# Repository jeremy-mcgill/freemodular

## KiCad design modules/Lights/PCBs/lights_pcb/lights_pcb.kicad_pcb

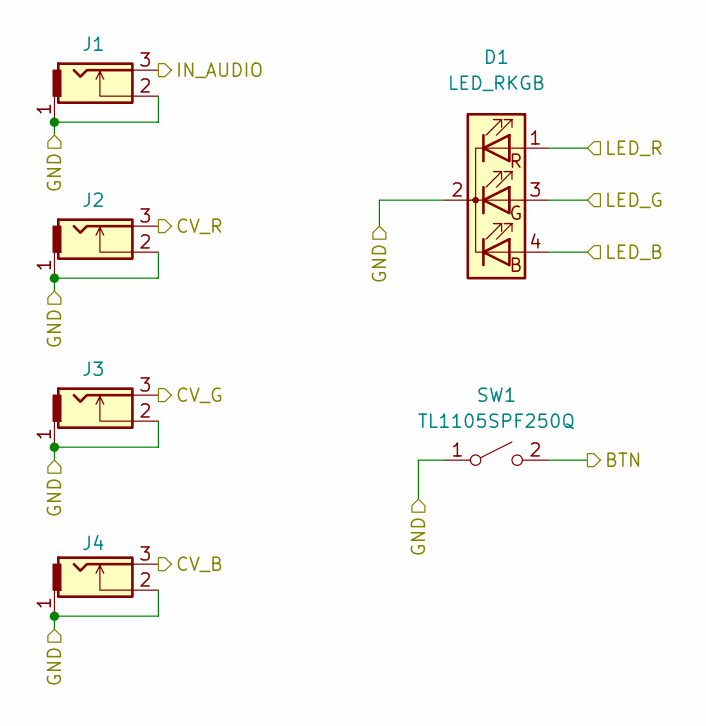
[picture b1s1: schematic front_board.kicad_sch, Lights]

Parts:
D1: LED_RKGB; LED_D5.0mm-4_RGB
J1, J2, J3, J4: THONKICONN
SW1: TL1105SPF250Q; SW_PUSH_6mm_H13mm

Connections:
/Front Board/BTN: SW1.2 (B); also elsewhere on the board
/Front Board/CV_B: J4.3; also elsewhere on the board
/Front Board/CV_G: J3.3; also elsewhere on the board
/Front Board/CV_R: J2.3; also elsewhere on the board
/Front Board/GND: D1.2 (K), J1.1, J1.2, J2.1, J2.2, J3.1, J3.2, J4.1, J4.2, SW1.1 (A); also elsewhere on the board
/Front Board/IN_AUDIO: J1.3; also elsewhere on the board
/Front Board/LED_B: D1.4 (BA); also elsewhere on the board
/Front Board/LED_G: D1.3 (GA); also elsewhere on the board
/Front Board/LED_R: D1.1 (RA); also elsewhere on the board

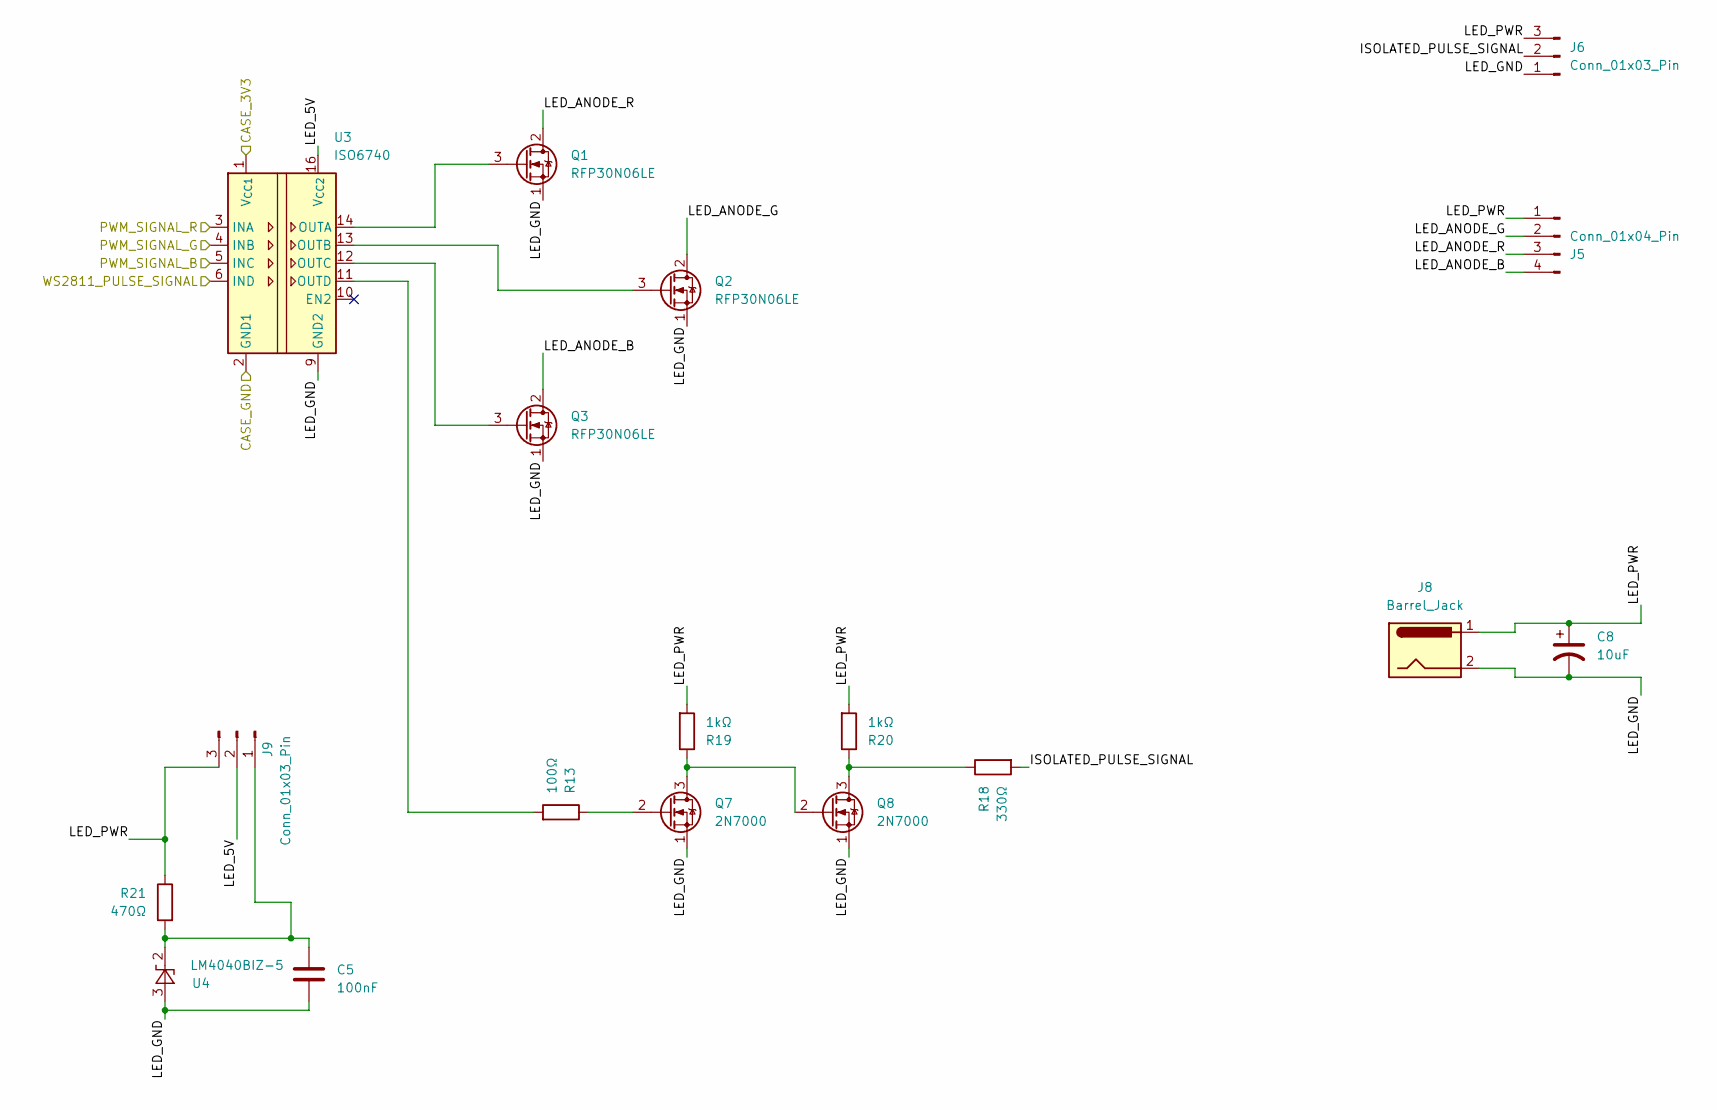
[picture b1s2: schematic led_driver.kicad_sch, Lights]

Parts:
C5: 100nF; C_Disc_D5.0mm_W2.5mm_P5.00mm
C8: 10uF; CP_Radial_D4.0mm_P1.50mm
J5: Conn_01x04_Pin; PinSocket_1x04_P2.54mm_Vertical
J6, J9: Conn_01x03_Pin; PinSocket_1x03_P2.54mm_Vertical
J8: Barrel_Jack; BarrelJack_Wuerth_6941xx301002
Q1, Q2, Q3: RFP30N06LE; TO-220-3_Vertical
Q7, Q8: 2N7000; TO-92_Inline
R13: 100Ω; R_Axial_DIN0207_L6.3mm_D2.5mm_P7.62mm_Horizontal
R18: 330Ω; R_Axial_DIN0207_L6.3mm_D2.5mm_P7.62mm_Horizontal
R19, R20: 1kΩ; R_Axial_DIN0207_L6.3mm_D2.5mm_P7.62mm_Horizontal
R21: 470Ω; R_Axial_DIN0207_L6.3mm_D2.5mm_P7.62mm_Horizontal
U3: ISO6740; SOIC-16W_7.5x10.3mm_P1.27mm
U4: LM4040BIZ-5; TO-92_Inline_Wide

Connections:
/Rear Board/+3.3V: U3.1 (V_{CC1}); also elsewhere on the board
/Rear Board/GND: U3.2 (GND1), U3.8 (GND1); also elsewhere on the board
/Rear Board/LED Driver/ISOLATED_PULSE_SIGNAL: J6.2, R18.2
/Rear Board/LED Driver/LED_5V: J9.2, U3.16 (V_{CC2})
/Rear Board/LED Driver/LED_ANODE_B: J5.4, Q3.2 (D)
/Rear Board/LED Driver/LED_ANODE_G: J5.2, Q2.2 (D)
/Rear Board/LED Driver/LED_ANODE_R: J5.3, Q1.2 (D)
/Rear Board/LED Driver/LED_GND: C5.2, C8.2, J6.1, J8.2, Q1.1 (S), Q2.1 (S), Q3.1 (S), Q7.1 (S), Q8.1 (S), U3.9 (GND2), U3.15 (GND2), U4.3 (A)
/Rear Board/LED Driver/LED_PWR: C8.1, J5.1, J6.3, J8.1, J9.3, R19.2, R20.2, R21.1
/Rear Board/LED_PULSE_SIGNAL: U3.6 (IND); also elsewhere on the board
/Rear Board/PWM_SIGNAL_B: U3.5 (INC); also elsewhere on the board
/Rear Board/PWM_SIGNAL_G: U3.4 (INB); also elsewhere on the board
/Rear Board/PWM_SIGNAL_R: U3.3 (INA); also elsewhere on the board
unnamed: C5.1, J9.1, R21.2, U4.2 (K)
unnamed: Q1.3 (G), U3.14 (OUTA)
unnamed: Q2.3 (G), U3.13 (OUTB)
unnamed: Q3.3 (G), U3.12 (OUTC)
unnamed: Q7.3 (D), Q8.2 (G), R19.1
unnamed: Q7.2 (G), R13.1
unnamed: Q8.3 (D), R18.1, R20.1
unnamed: R13.2, U3.11 (OUTD)

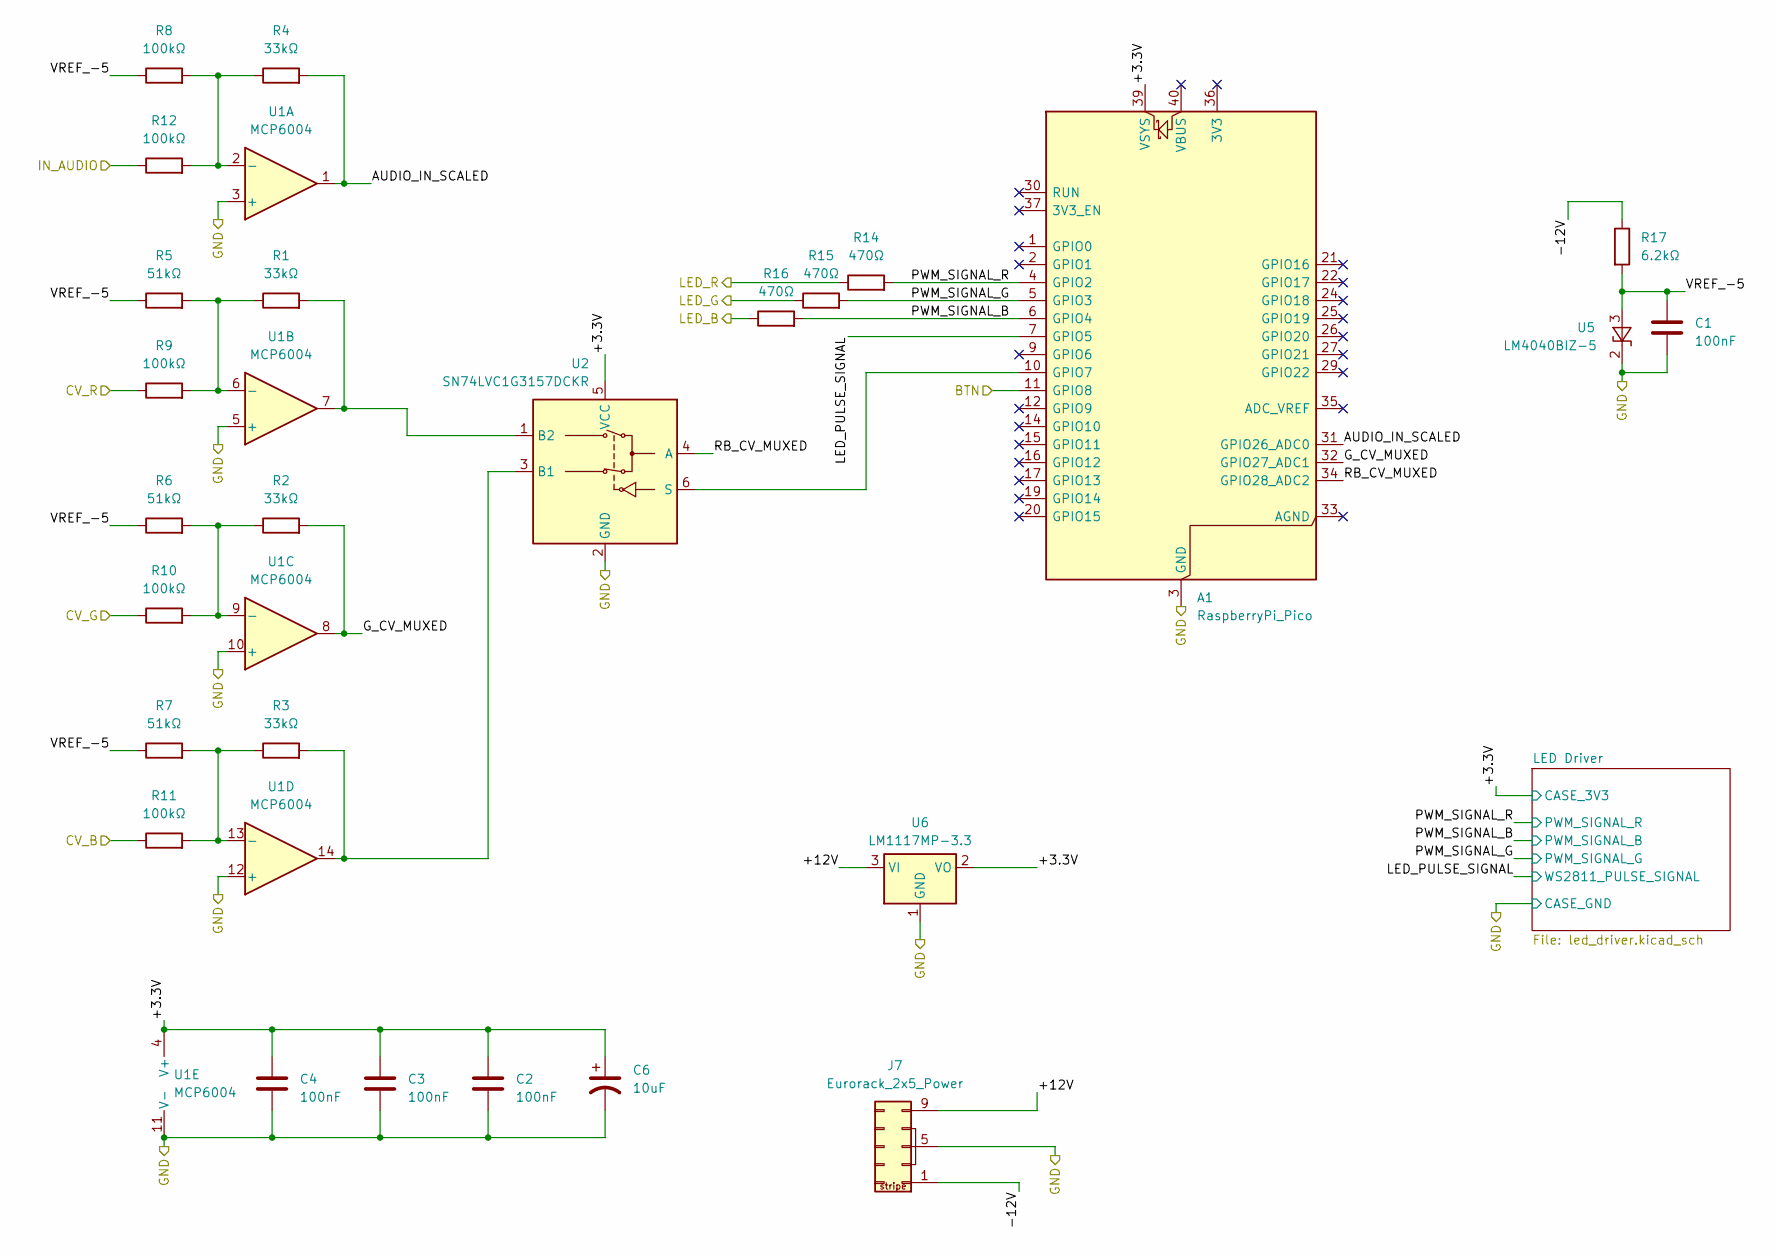
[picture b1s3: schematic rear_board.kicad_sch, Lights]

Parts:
A1: RaspberryPi_Pico; RaspberryPi_Pico_Common_Unspecified
C1, C2, C3, C4: 100nF; C_Disc_D5.0mm_W2.5mm_P5.00mm
C6: 10uF; CP_Radial_D4.0mm_P1.50mm
J7: Eurorack_2x5_Power; IDC-Header_2x05_P2.54mm_Vertical
R1, R2, R3, R4: 33kΩ; R_Axial_DIN0207_L6.3mm_D2.5mm_P7.62mm_Horizontal
R5, R6, R7: 51kΩ; R_Axial_DIN0207_L6.3mm_D2.5mm_P7.62mm_Horizontal
R8, R9, R10, R11, R12: 100kΩ; R_Axial_DIN0207_L6.3mm_D2.5mm_P7.62mm_Horizontal
R14, R15, R16: 470Ω; R_Axial_DIN0207_L6.3mm_D2.5mm_P7.62mm_Horizontal
R17: 6.2kΩ; R_Axial_DIN0207_L6.3mm_D2.5mm_P7.62mm_Horizontal
U1: MCP6004; DIP-14_W7.62mm
U2: SN74LVC1G3157DCKR; SOT-363_SC-70-6_Handsoldering
U5: LM4040BIZ-5; TO-92_Inline_Wide
U6: LM1117MP-3.3; SOT-223-3_TabPin2

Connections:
/Rear Board/+3.3V: A1.39 (VSYS), C2.1, C3.1, C4.1, C6.1, U1.4 (V+), U2.5 (VCC), U6.2 (VO); also elsewhere on the board
/Rear Board/+12V: J7.9 (+12v), J7.10 (+12v), U6.3 (VI)
/Rear Board/-12V: J7.1 (-12v), J7.2 (-12v), R17.1
/Rear Board/AUDIO_IN_SCALED: A1.31 (GPIO26_ADC0), R4.2, U1.1
/Rear Board/BTN: A1.11 (GPIO8); also elsewhere on the board
/Rear Board/CV_B: R11.1; also elsewhere on the board
/Rear Board/CV_G: R10.1; also elsewhere on the board
/Rear Board/CV_R: R9.1; also elsewhere on the board
/Rear Board/GND: A1.3 (GND), A1.8 (GND), A1.13 (GND), A1.18 (GND), A1.23 (GND), A1.28 (GND), A1.38 (GND), C1.2, C2.2, C3.2, C4.2, C6.2, J7.3 (GND), J7.4 (GND), J7.5 (GND), J7.6 (GND), J7.7 (GND), J7.8 (GND), U1.3 (+), U1.5 (+), U1.10 (+), U1.11 (V-), U1.12 (+), U2.2 (GND), U5.2 (K), U6.1 (GND); also elsewhere on the board
/Rear Board/G_CV_MUXED: A1.32 (GPIO27_ADC1), R2.2, U1.8
/Rear Board/IN_AUDIO: R12.1; also elsewhere on the board
/Rear Board/LED_B: R16.1; also elsewhere on the board
/Rear Board/LED_G: R15.1; also elsewhere on the board
/Rear Board/LED_PULSE_SIGNAL: A1.7 (GPIO5); also elsewhere on the board
/Rear Board/LED_R: R14.1; also elsewhere on the board
/Rear Board/PWM_SIGNAL_B: A1.6 (GPIO4), R16.2; also elsewhere on the board
/Rear Board/PWM_SIGNAL_G: A1.5 (GPIO3), R15.2; also elsewhere on the board
/Rear Board/PWM_SIGNAL_R: A1.4 (GPIO2), R14.2; also elsewhere on the board
/Rear Board/RB_CV_MUXED: A1.34 (GPIO28_ADC2), U2.4 (A)
/Rear Board/VREF_-5: C1.1, R5.1, R6.1, R7.1, R8.1, R17.2, U5.3 (A)
unnamed: A1.10 (GPIO7), U2.6 (S)
unnamed: R4.1, R8.2, R12.2, U1.2 (-)
unnamed: R1.1, R5.2, R9.2, U1.6 (-)
unnamed: R2.1, R6.2, R10.2, U1.9 (-)
unnamed: R3.1, R7.2, R11.2, U1.13 (-)
unnamed: R3.2, U1.14, U2.3 (B1)
unnamed: R1.2, U1.7, U2.1 (B2)

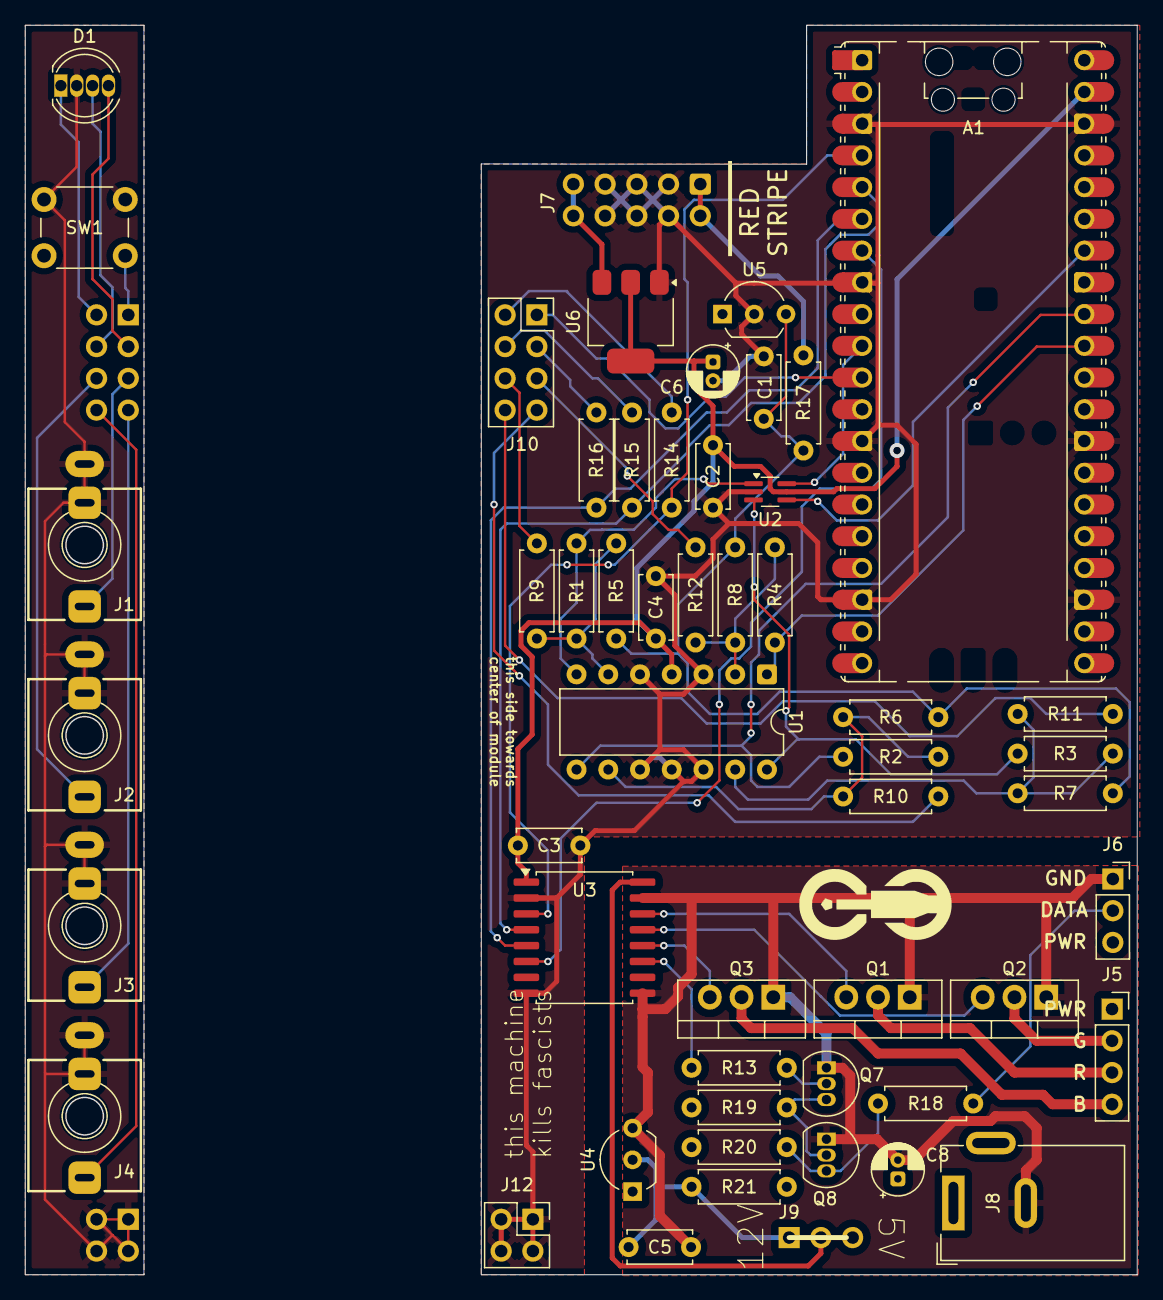
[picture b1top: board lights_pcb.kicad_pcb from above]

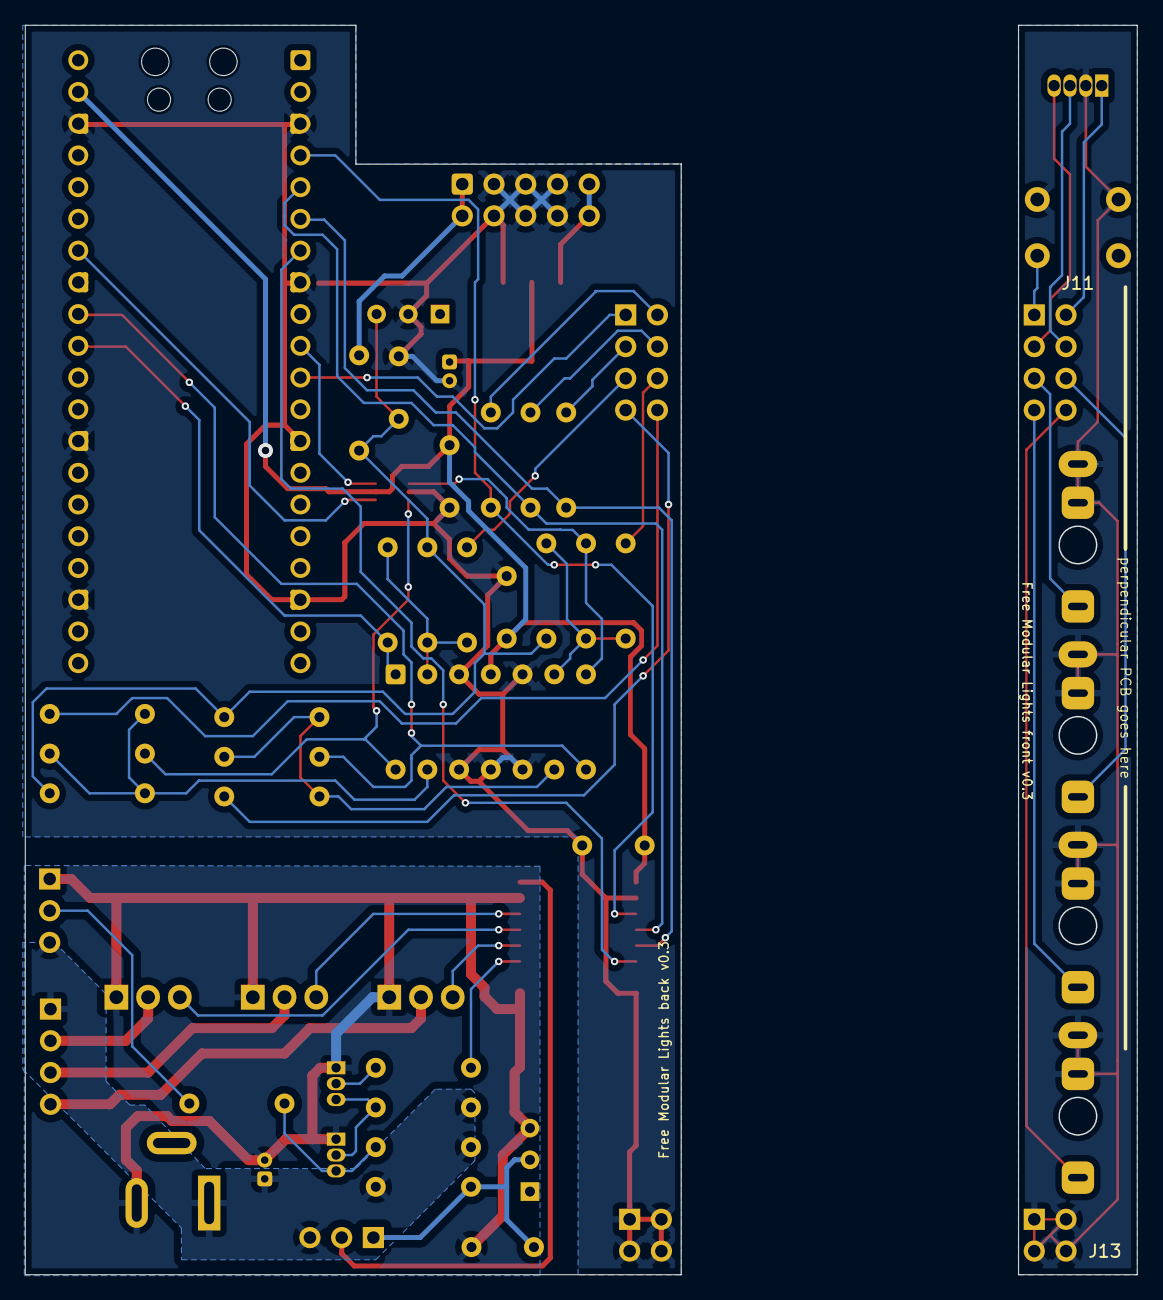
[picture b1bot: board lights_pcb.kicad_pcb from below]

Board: 2 copper layers, 52.5 x 100.0 mm, 58 parts (2 on the bottom side), 51 nets.

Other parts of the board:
B1, B2: Board
G1: logo_small
J10: Conn_02x04_Top_Bottom; PinSocket_2x04_P2.54mm_Vertical
J11: Conn_02x04_Top_Bottom; PinHeader_2x04_P2.54mm_Horizontal
J12: Conn_02x02_Top_Bottom; PinSocket_2x02_P2.54mm_Vertical
J13: Conn_02x02_Top_Bottom; PinHeader_2x02_P2.54mm_Horizontal

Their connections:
/Front Board/BTN: J11.1; also elsewhere on the board
/Front Board/CV_B: J11.8; also elsewhere on the board
/Front Board/CV_G: J11.7; also elsewhere on the board
/Front Board/CV_R: J11.6; also elsewhere on the board
/Front Board/GND: J13.1, J13.2, J13.3, J13.4; also elsewhere on the board
/Front Board/IN_AUDIO: J11.5; also elsewhere on the board
/Front Board/LED_B: J11.3; also elsewhere on the board
/Front Board/LED_G: J11.4; also elsewhere on the board
/Front Board/LED_R: J11.2; also elsewhere on the board
/Rear Board/BTN: J10.1; also elsewhere on the board
/Rear Board/CV_B: J10.8; also elsewhere on the board
/Rear Board/CV_G: J10.7; also elsewhere on the board
/Rear Board/CV_R: J10.6; also elsewhere on the board
/Rear Board/GND: J12.1, J12.2, J12.3, J12.4; also elsewhere on the board
/Rear Board/IN_AUDIO: J10.5; also elsewhere on the board
/Rear Board/LED_B: J10.3; also elsewhere on the board
/Rear Board/LED_G: J10.4; also elsewhere on the board
/Rear Board/LED_R: J10.2; also elsewhere on the board

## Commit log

2025-11-12 Switch lights to external 3.3V power supply instead of using rpi pico
2025-12-06 working on harmonic simplex terrain mode
2026-01-18 Change compiler config to optimize for file size
2026-01-18 Add channel trigger probability
2026-01-18 Fix strange menu editing behaviour
2026-01-19 fm-lib: allow inverting RotaryEncoder direction
2026-01-19 Feature: hold encoder button at startup to invert encoder direction
